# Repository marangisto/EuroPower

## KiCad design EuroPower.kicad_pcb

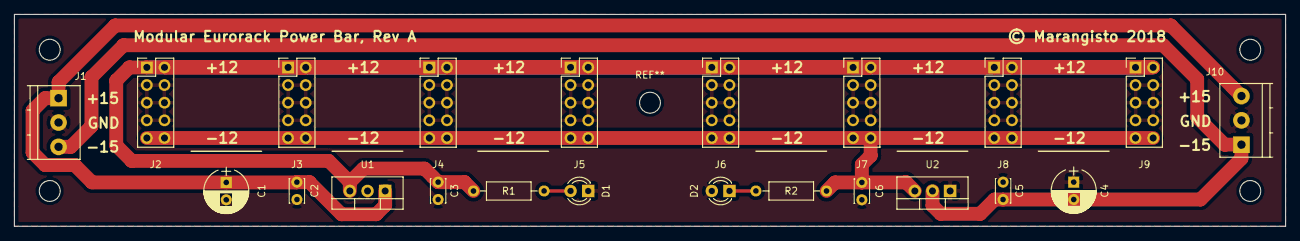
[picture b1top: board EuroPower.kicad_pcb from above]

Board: 2 copper layers, 182.9 x 30.5 mm, 22 parts (0 on the bottom side), 7 nets.

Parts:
C1, C4: 10u; CP_Radial_D6.3mm_P2.50mm
C2, C3, C5, C6: 100n; C_Disc_D3.4mm_W2.1mm_P2.50mm
D1, D2: LED; LED_D3.0mm
J1, J10: Screw_Terminal_01x03; TerminalBlock_Phoenix_PT-3.5mm_3pol
J2, J3, J4, J5, J6, J7, J8, J9: Conn_02x05_Odd_Even; Pin_Header_Straight_2x05_Pitch2.54mm
R1, R2: 1k; R_Axial_DIN0207_L6.3mm_D2.5mm_P10.16mm_Horizontal
U1: LM7812_TO220; TO-220-3_Vertical
U2: LM7912_TO220; TO-220-3_Vertical

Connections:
+12V: C3.1, J2.1, J2.2, J3.1, J3.2, J4.1, J4.2, J5.1, J5.2, J6.1, J6.2, J7.1, J7.2, J8.1, J8.2, J9.1, J9.2, R1.1, U1.3
-12V: C6.2, J2.9, J2.10, J3.9, J3.10, J4.9, J4.10, J5.9, J5.10, J6.9, J6.10, J7.9, J7.10, J8.9, J8.10, J9.9, J9.10, R2.2, U2.3
GND: C1.2, C2.2, C3.2, C4.1, C5.1, C6.1, D1.1, D2.2, J1.2, J2.3, J2.4, J2.5, J2.6, J2.7, J2.8, J3.3, J3.4, J3.5, J3.6, J3.7, J3.8, J4.3, J4.4, J4.5, J4.6, J4.7, J4.8, J5.3, J5.4, J5.5, J5.6, J5.7, J5.8, J6.3, J6.4, J6.5, J6.6, J6.7, J6.8, J7.3, J7.4, J7.5, J7.6, J7.7, J7.8, J8.3, J8.4, J8.5, J8.6, J8.7, J8.8, J9.3, J9.4, J9.5, J9.6, J9.7, J9.8, J10.2, U1.2, U2.1
unnamed: C1.1, C2.1, J1.1, J10.3, U1.1
unnamed: C4.2, C5.2, J1.3, J10.1, U2.2
unnamed: D1.2, R1.2
unnamed: D2.1, R2.1

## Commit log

2018-07-23 Initial schematic.
2018-07-23 Updated resistor values.
2018-07-23 Assigned footprints.
2018-07-23 Added power flags, clean DRC for schematic.
2018-07-24 Initial PCB.
2018-07-25 Daisy-chainable design.
2018-07-25 Routed power lines.
2018-07-25 Added dimensions (again).
2018-07-25 Ground pours.
2018-07-25 Silkscreen layout.
2018-07-25 Posted gerbers.
2018-07-25 Save gerber settings.
2018-07-25 Added rendering.
2018-07-31 Added bom.
2018-08-04 Upgraded to KiCad 5.
2018-08-06 Corrected some dimensions.

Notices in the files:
EuroPower.kicad_pcb:
© Marangisto 2018
